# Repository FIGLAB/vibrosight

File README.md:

# Vibrosight
This repository contains source files for the project Vibrosight. The research publication and more details of this project can be found here: https://yangzhang.dev/research/Vibrosight/Vibrosight.pdf

Project video can be found here: https://youtu.be/51XaZDki6yg

## Usage

We uploaded all data collected in the evaluation session and wrote a visualizer to render the data offline. To run the visualizer, please download the repository and execute the pre-compiled visualizer code (i.e., ./data and visualizer/visualizer.jar). 

## Other resources
The hardware folder contains the Eagle PCB design files, including the schematic and the PCB layout:

The firmware is based on [Teensy 3.2](https://www.pjrc.com/teensy/teensy31.html) and can be edited and compiled with the [Arduino](https://www.arduino.cc) IDE. 

A real-time visualzer that visualize data streamed from the sensor board:

The 3D prints folder contains the model design files for the mirror-control platform:

## Known issues
The software was tested on MacBook (MacOS 10.14.5). For window systems the sensor board will enumerate with different names, which need to be updated in ./software/src/serial/SerialReader.java (line 28).

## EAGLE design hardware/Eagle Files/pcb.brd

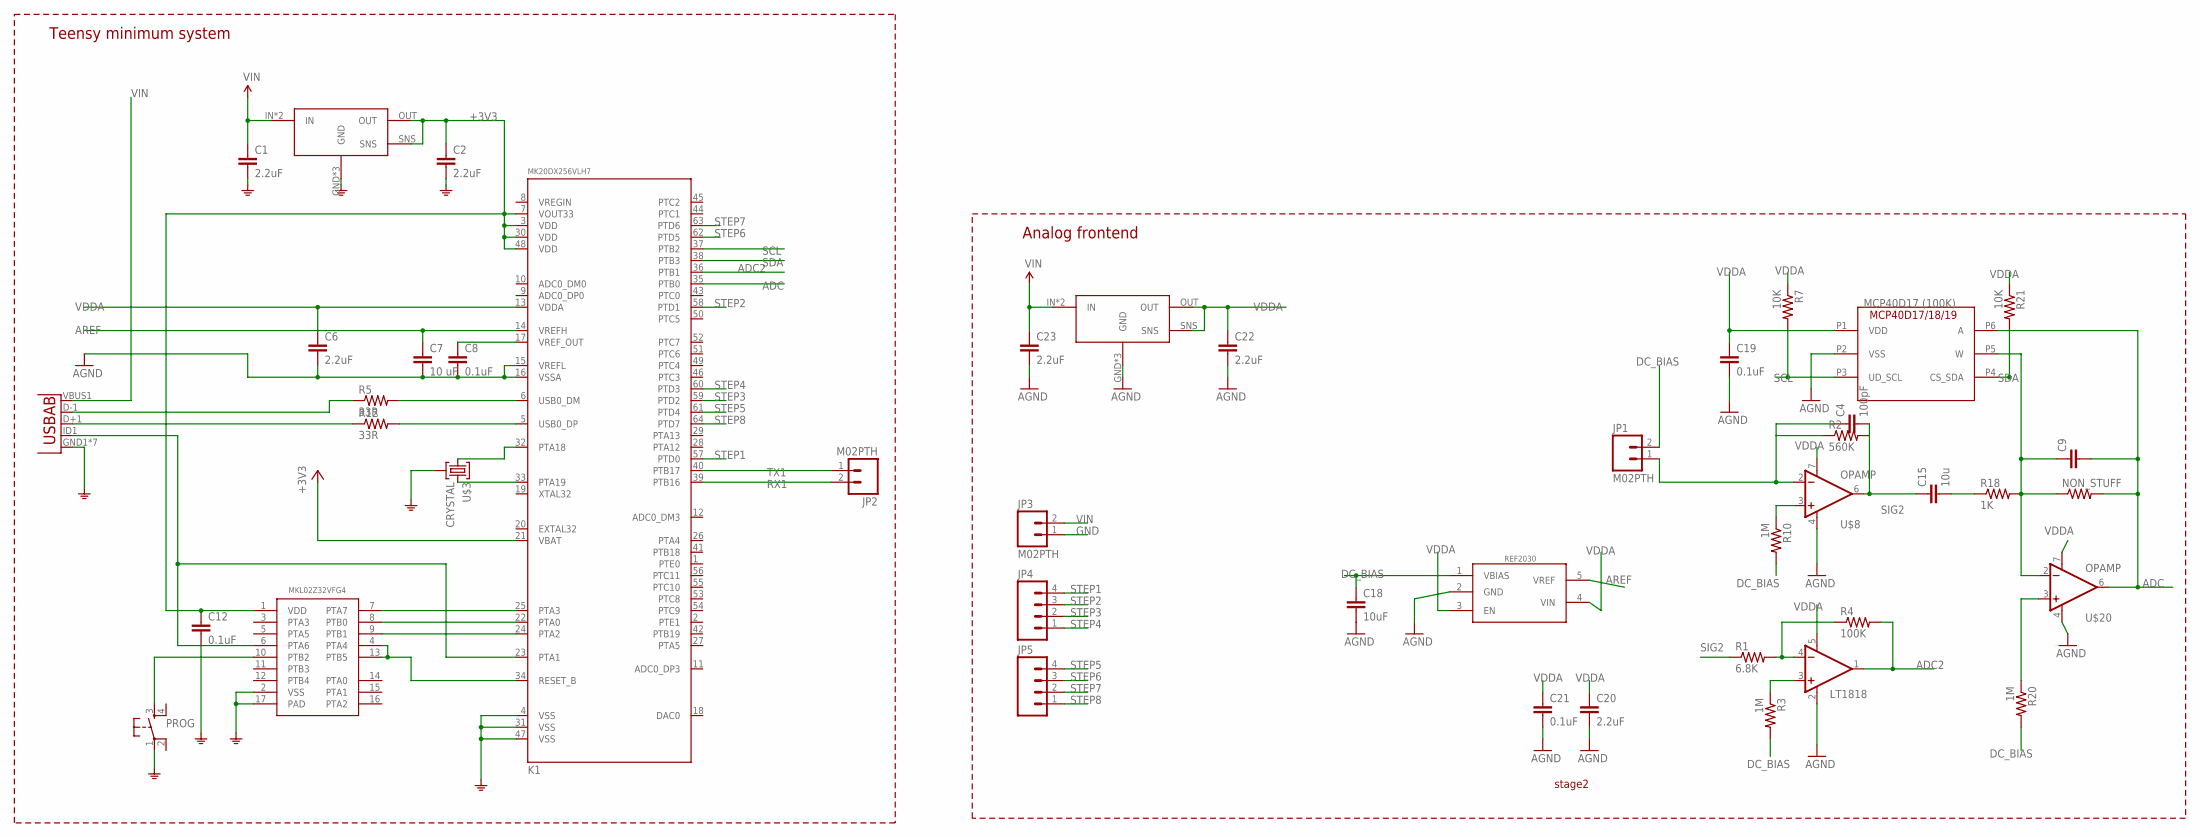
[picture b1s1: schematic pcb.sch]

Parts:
C1, C2, C6, C22, C23: 2.2uF; 0402-CAP
C4: 100pF; 0402-CAP
C7: 10 uF; 0402-CAP
C8, C12, C19, C21: 0.1uF; 0402-CAP
C9: C-EUC0402; C0402
C15: 10u; C0402
C18: 10uF; 0402-CAP
C20: 2.2uF; 0603-CAP
JP1, JP2, JP3: M02PTH; 1X02
JP4, JP5: M04PTH; 1X04
K1: MK20DX256VLH7; LQFP64-05
LP1, LP38691: LP38691SD; WSON_6
NON_STUFF: RESISTOR0402; 0402-RES
PROG: KMR211GLFS; TACTILE_SWITCH_SMD
R1: 6.8K; 0402-RES
R2: 560K; 0402-RES
R3, R10, R20: 1M; 0402-RES
R4: 100K; 0402-RES
R5, R12: 33R; 0402-RES
R7, R21: 10K; 0402-RES
R18: 1K; 0402-RES
REF2030: REF2033; SOT23
U5: USB""; USB-MICRO-SMD
U14: LT1818; SOT23-5
U$3: CRYSTAL
U$6: MCP40D17/18/19; SC70-6
U$8, U$20: OPAMP; 8-SOIC
U$14: MKL02Z32VFG4_; QFN16_3X3

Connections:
+3V3: C2.1, C12.1, K1.3 (VDD), K1.7 (VOUT33), K1.21 (VBAT), K1.30 (VDD), K1.48 (VDD), LP38691.OUT, LP38691.SNS, U$14.1 (VDD)
ADC: C9.2, K1.35 (PTB0), NON_STUFF.2, U$6.P6 (A), U$20.6 (OUT)
ADC2: K1.36 (PTB1), R4.2, U14.1 (OUT)
AGND: C6.2, C7.2, C8.2, C18.2, C19.2, C20.2, C21.2, C22.2, C23.2, K1.15 (VREFL), K1.16 (VSSA), LP1.GND, LP1.N/C (GND), LP1.THERMAL (GND), REF2030.2 (GND), U14.2 (V-), U$6.P2 (VSS), U$8.4 (V-), U$20.4 (V-)
AREF: C7.1, K1.14 (VREFH), REF2030.5 (VREF)
DC_BIAS: C18.1, JP1.2, R3.2, R10.2, R20.2, REF2030.1 (VBIAS)
GND: C1.2, C2.2, C12.2, JP3.1, K1.4 (VSS), K1.31 (VSS), K1.47 (VSS), LP38691.GND, LP38691.N/C (GND), LP38691.THERMAL (GND), PROG.1, U5.GND1 (GND), U5.P$1 (GND), U5.P$2 (GND), U5.P$3 (GND), U5.P$4 (GND), U5.P$5 (GND), U5.P$6 (GND), U$3.GND1 (2), U$3.GND2 (2), U$14.2 (VSS), U$14.17 (PAD)
unnamed: C4.1, JP1.1, R2.1, U$8.2 (-IN)
unnamed: R1.2, R4.1, U14.4 (-IN)
unnamed: C9.1, NON_STUFF.1, R18.2, U$6.P5 (W), U$20.2 (-IN)
unnamed: K1.32 (PTA18), U$3.SIG1 (1)
unnamed: K1.33 (PTA19), U$3.SIG2 (3)
unnamed: K1.24 (PTA2), U$14.9 (PTB1)
unnamed: R10.1, U$8.3 (+IN)
unnamed: K1.22 (PTA0), U$14.8 (PTB0)
unnamed: R3.1, U14.3 (+IN)
unnamed: C8.1, K1.17 (VREF_OUT)
unnamed: C15.2, R18.1
unnamed: K1.5 (USB0_DP), R12.2
unnamed: K1.6 (USB0_DM), R5.2
unnamed: R12.1, U5.D+1 (D+)
unnamed: R5.1, U5.D-1 (D-)
unnamed: K1.23 (PTA1), U5.ID1 (USBID), U$14.6 (PTA6)
unnamed: R20.1, U$20.3 (+IN)
unnamed: PROG.3, U$14.10 (PTB2)
unnamed: K1.25 (PTA3), U$14.7 (PTA7)
RST: K1.34 (RESET_B), U$14.4 (PTA4), U$14.13 (PTB5)
RX1: JP2.2, K1.39 (PTB16)
SCL: K1.37 (PTB2), R7.2, U$6.P3 (UD_SCL)
SDA: K1.38 (PTB3), R21.2, U$6.P4 (CS_SDA)
SIG2: C4.2, C15.1, R1.1, R2.2, U$8.6 (OUT)
STEP1: JP4.4, K1.57 (PTD0)
STEP2: JP4.3, K1.58 (PTD1)
STEP3: JP4.2, K1.59 (PTD2)
STEP4: JP4.1, K1.60 (PTD3)
STEP5: JP5.4, K1.61 (PTD4)
STEP6: JP5.3, K1.62 (PTD5)
STEP7: JP5.2, K1.63 (PTD6)
STEP8: JP5.1, K1.64 (PTD7)
TX1: JP2.1, K1.40 (PTB17)
VDDA: C6.1, C19.1, C20.1, C21.1, C22.1, K1.13 (VDDA), LP1.OUT, LP1.SNS, R7.1, R21.1, REF2030.3 (EN), REF2030.4 (VIN), U14.5 (V+), U$6.P1 (VDD), U$8.7 (V+), U$20.7 (V+)
VIN: C1.1, C23.1, JP3.2, LP1.IN, LP1.IN2 (IN), LP38691.IN, LP38691.IN2 (IN), U5.VBUS1 (VBUS)

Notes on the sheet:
Teensy minimum system
Analog frontend
MCP40D17 (100K)
stage2

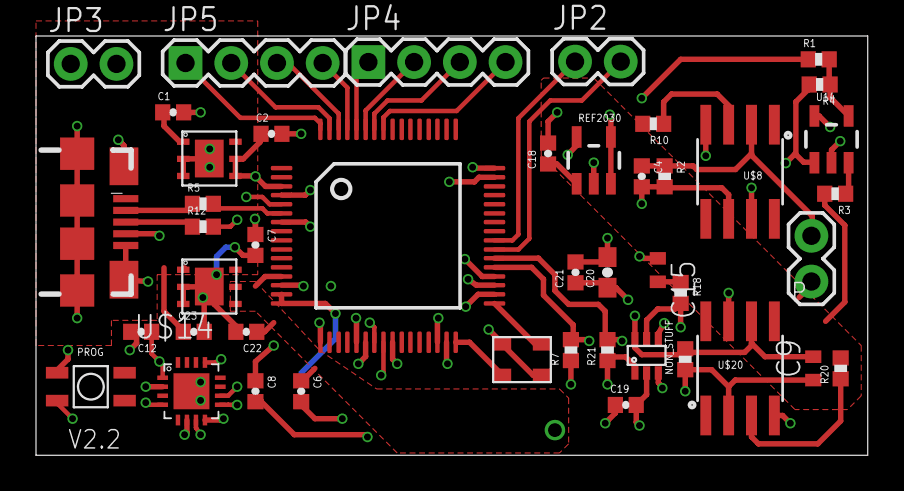
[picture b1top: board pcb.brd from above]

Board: 4 copper layers, 46.2 x 23.3 mm, 44 parts (0 on the bottom side), 42 nets.

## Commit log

2018-07-05 Added README and images.
2018-07-05 Added hardware design files and datasheets.
2018-07-05 Added 3D print MakerBot file
2018-07-05 Added firmware
2018-07-26 Ported data and visualizer
2018-10-14 Added the latest software code with comments
2018-10-14 Updated ReadMe file
2018-10-15 Added UI for visualizing Vibrosight signals
2019-02-05 removed redundant software code
2019-06-10 change for TeamZ trip
2019-06-10 Revert "change for TeamZ trip"
    This reverts commit 97e59d618e21542305b762cd5ba13221074f8e74.
2019-07-26 Updated license from GPL3.0 to GPL2.0
2019-08-02 Update README.md
    Updated the project webpage and added known issues.
2019-09-10 Updated the firmware code to be compatible with teensyduino 1.47 (latest)

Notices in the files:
parts and their libraries:
SparkFun-Capacitors: Licensing: Creative Commons ShareAlike 4.0 International - https://creativecommons.org/licenses/by-sa/4.0
